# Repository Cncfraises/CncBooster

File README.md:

# CncBooster
CncBooster est un interpolateur USB basé sur le projet TinyG de Synthetos.

CncBooster is an usb motion controller board based on Synthetos TinyG project.

Christophe / 2015

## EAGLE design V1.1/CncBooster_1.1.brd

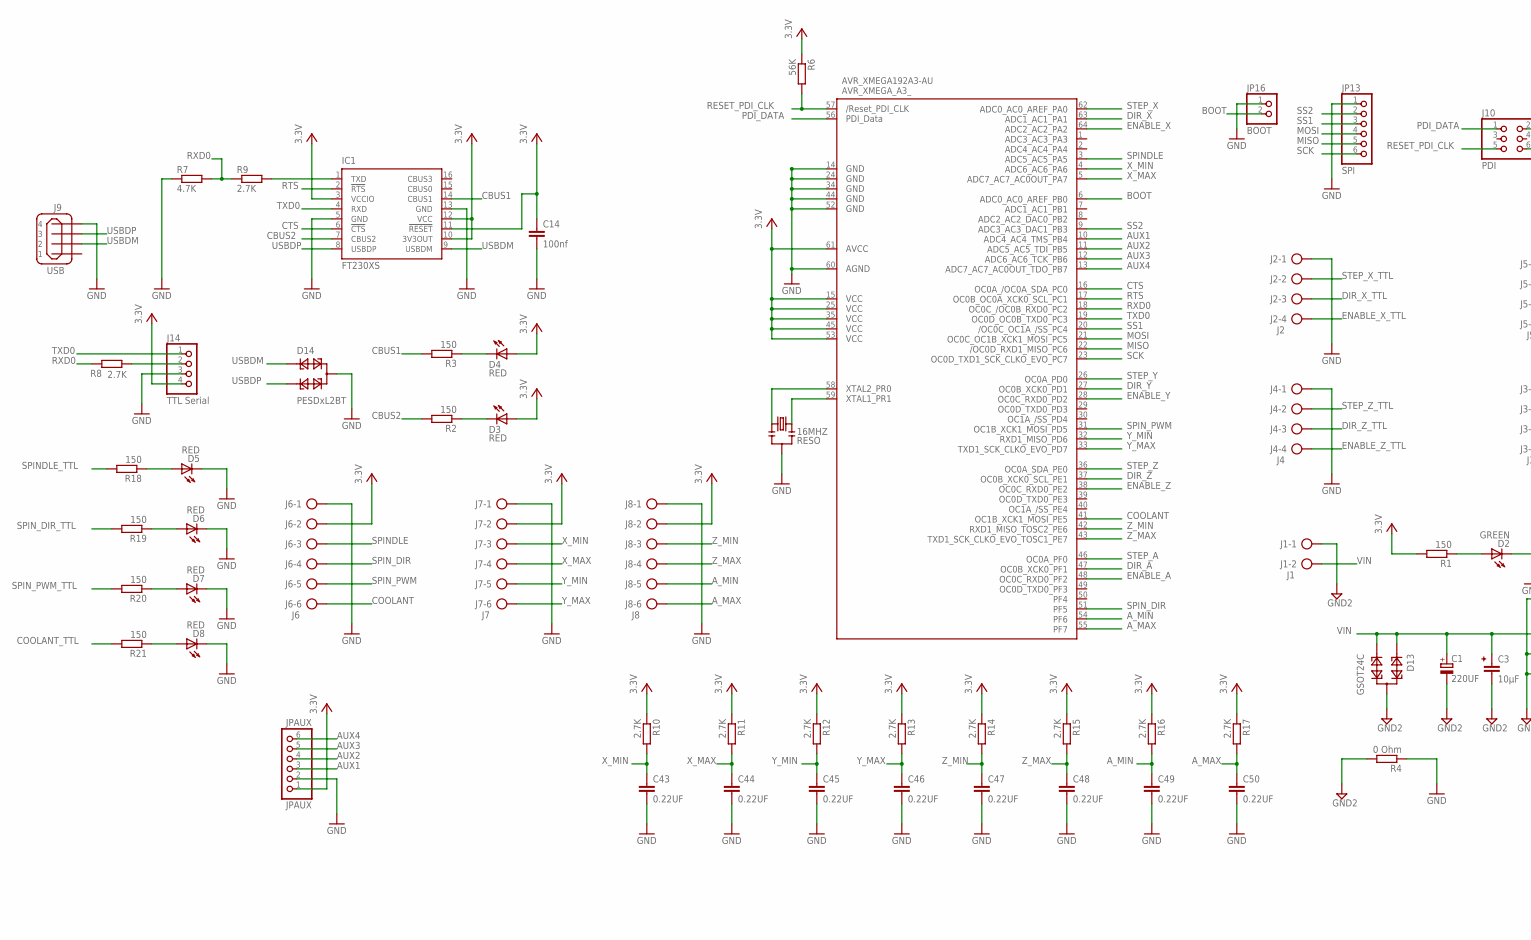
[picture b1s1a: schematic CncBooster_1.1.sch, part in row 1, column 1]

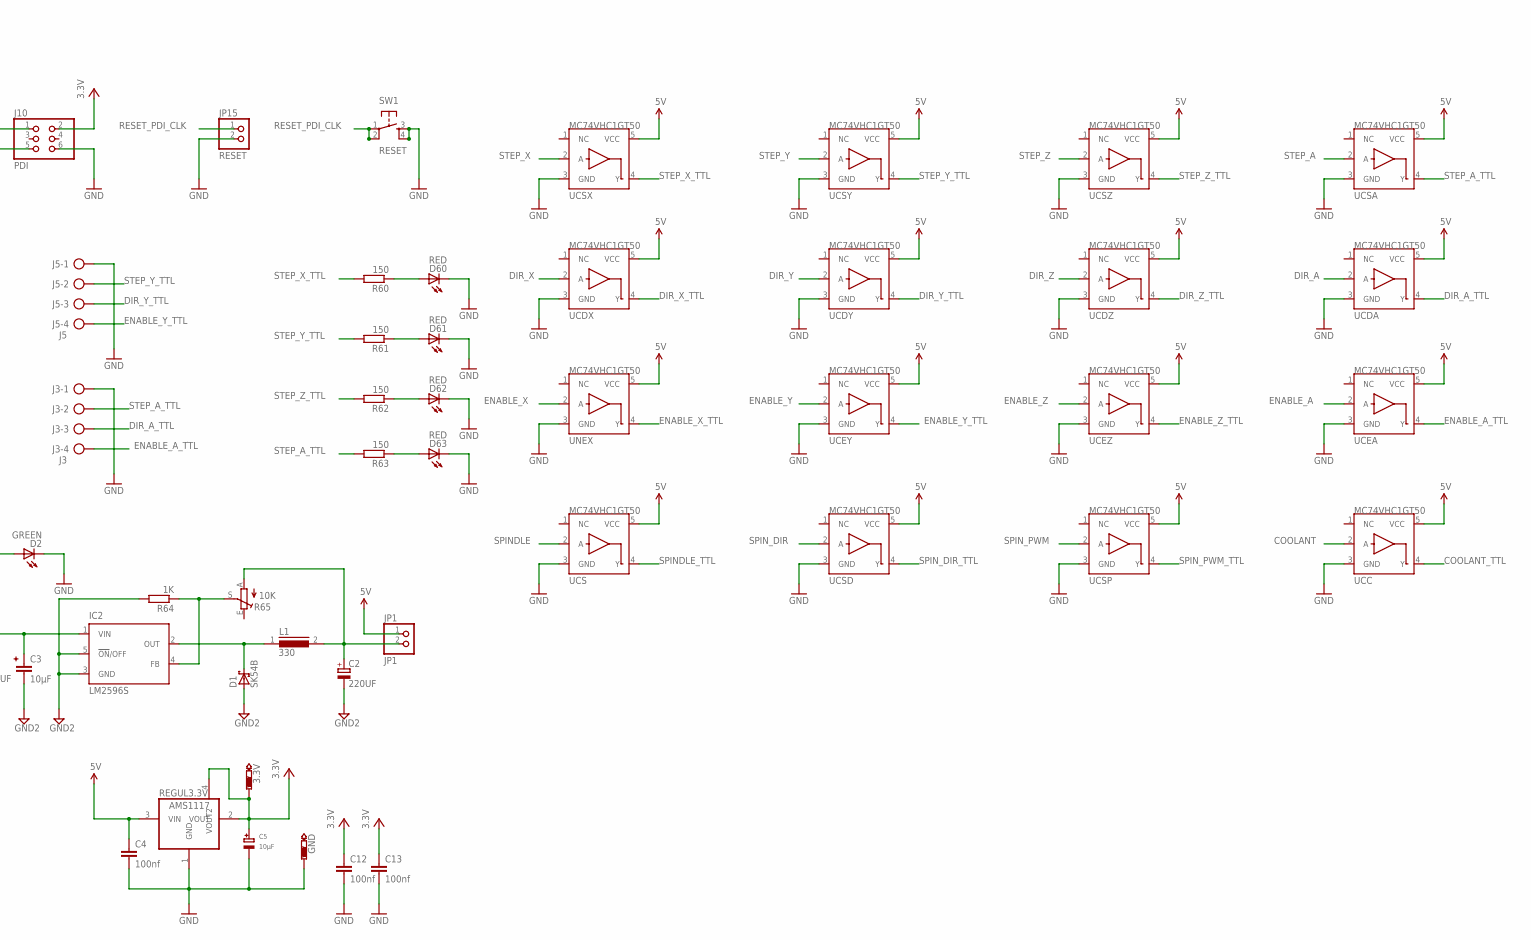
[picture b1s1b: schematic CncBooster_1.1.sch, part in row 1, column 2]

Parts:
3.3V: PTR1B1,27; B1,27
16MHZ: RESO; RESONATOR_CMS_AWSCR
AVR_XMEGA192A3-AU: AVR_XMEGA_A3_; TQFP64
C1, C2: 220UF; PANASONIC_E
C3: 10µF; CONDO_1206
C4, C12, C13, C14: 100nf; C1206
C5: 10µF; EIA3216-18/A-W
C43, C44, C45, C46, C47, C48, C49, C50: 0.22UF; C1206
D1: SK54B; DO-214AA
D2: GREEN; CHIPLED_1206
D3, D4, D5, D6, D7, D8, D60, D61, D62, D63: RED; CHIPLED_1206
D13: GSOT24C; SOT23
D14: PESDxL2BT; SOT23
GND: PTR1B1,27; B1,27
IC1: FT230XS; SSOP16
IC2: LM2596S; TO263-5
J1: J1; AK500/2
J2: J2; AK500/4
J3: J3; AK500/4
J4: J4; AK500/4
J5: J5; AK500/4
J6: J6; AK500/6
J7: J7; AK500/6
J8: J8; AK500/6
J9: USB; 85-32004-10X
J10: PDI; 2X03
J14: TTL Serial; 1X04
JP1: JP1; 1X02
JP13: SPI; 1X06
JP15: RESET; 1X02
JP16: BOOT; 1X02
JPAUX: JPAUX; 1X06
L1: 330; DR127
R1, R2, R3, R18, R19, R20, R21, R60, R61, R62, R63: 150; R1206
R4: 0 Ohm; R1206
R6: 56K; R1206
R7: 4.7K; R1206
R8, R9, R10, R11, R12, R13, R14, R15, R16, R17: 2.7K; R1206
R64: 1K; R1206
R65: 10K; S64W
REGUL3.3V: AMS1117; SOT223-A
SW1: RESET; TACTILE_SWITCH_SMD
UCC: MC74VHC1GT50; SOT23-5
UCDA: MC74VHC1GT50; SOT23-5
UCDX: MC74VHC1GT50; SOT23-5
UCDY: MC74VHC1GT50; SOT23-5
UCDZ: MC74VHC1GT50; SOT23-5
UCEA: MC74VHC1GT50; SOT23-5
UCEY: MC74VHC1GT50; SOT23-5
UCEZ: MC74VHC1GT50; SOT23-5
UCS: MC74VHC1GT50; SOT23-5
UCSA: MC74VHC1GT50; SOT23-5
UCSD: MC74VHC1GT50; SOT23-5
UCSP: MC74VHC1GT50; SOT23-5
UCSX: MC74VHC1GT50; SOT23-5
UCSY: MC74VHC1GT50; SOT23-5
UCSZ: MC74VHC1GT50; SOT23-5
UNEX: MC74VHC1GT50; SOT23-5

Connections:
5V: C4.1, JP1.1, REGUL3.3V.3 (VIN), UCC.5 (VCC), UCDA.5 (VCC), UCDX.5 (VCC), UCDY.5 (VCC), UCDZ.5 (VCC), UCEA.5 (VCC), UCEY.5 (VCC), UCEZ.5 (VCC), UCS.5 (VCC), UCSA.5 (VCC), UCSD.5 (VCC), UCSP.5 (VCC), UCSX.5 (VCC), UCSY.5 (VCC), UCSZ.5 (VCC), UNEX.5 (VCC)
AUX1: AVR_XMEGA192A3-AU.10 (PB4), JPAUX.3
AUX2: AVR_XMEGA192A3-AU.11 (PB5), JPAUX.4
AUX3: AVR_XMEGA192A3-AU.12 (PB6), JPAUX.5
AUX4: AVR_XMEGA192A3-AU.13 (PB7), JPAUX.6
A_MAX: AVR_XMEGA192A3-AU.55 (PF7), C50.1, J8.6, R17.2
A_MIN: AVR_XMEGA192A3-AU.54 (PF6), C49.1, J8.5, R16.2
BOOT: AVR_XMEGA192A3-AU.6 (PB0), JP16.2
CBUS1: IC1.14 (CBUS1), R3.2
CBUS2: IC1.7 (CBUS2), R2.2
COOLANT: AVR_XMEGA192A3-AU.41 (PE5), J6.6, UCC.2 (A)
COOLANT_TTL: R21.2, UCC.4 (Y)
CTS: AVR_XMEGA192A3-AU.16 (PC0), IC1.6 (!CTS)
DIR_A: AVR_XMEGA192A3-AU.47 (PF1), UCDA.2 (A)
DIR_A_TTL: J3.3, UCDA.4 (Y)
DIR_X: AVR_XMEGA192A3-AU.63 (PA1), UCDX.2 (A)
DIR_X_TTL: J2.3, UCDX.4 (Y)
DIR_Y: AVR_XMEGA192A3-AU.27 (PD1), UCDY.2 (A)
DIR_Y_TTL: J5.3, UCDY.4 (Y)
DIR_Z: AVR_XMEGA192A3-AU.37 (PE1), UCDZ.2 (A)
DIR_Z_TTL: J4.3, UCDZ.4 (Y)
ENABLE_A: AVR_XMEGA192A3-AU.48 (PF2), UCEA.2 (A)
ENABLE_A_TTL: J3.4, UCEA.4 (Y)
ENABLE_X: AVR_XMEGA192A3-AU.64 (PA2), UNEX.2 (A)
ENABLE_X_TTL: J2.4, UNEX.4 (Y)
ENABLE_Y: AVR_XMEGA192A3-AU.28 (PD2), UCEY.2 (A)
ENABLE_Y_TTL: J5.4, UCEY.4 (Y)
ENABLE_Z: AVR_XMEGA192A3-AU.38 (PE2), UCEZ.2 (A)
ENABLE_Z_TTL: J4.4, UCEZ.4 (Y)
GND: 16MHZ.P$3 (2), AVR_XMEGA192A3-AU.14 (GND1), AVR_XMEGA192A3-AU.24 (GND2), AVR_XMEGA192A3-AU.34 (GND3), AVR_XMEGA192A3-AU.44 (GND4), AVR_XMEGA192A3-AU.52 (GND5), AVR_XMEGA192A3-AU.60 (AGND), C4.2, C5.-, C12.2, C13.2, C14.2, C43.2, C44.2, C45.2, C46.2, C47.2, C48.2, C49.2, C50.2, D2.C, D5.C, D6.C, D7.C, D8.C, D14.3, D60.C, D61.C, D62.C, D63.C, GND.TP, IC1.5 (GND), IC1.13 (GND), J2.1, J3.1, J4.1, J5.1, J6.1, J7.1, J8.1, J9.4, J10.6, J14.3, JP13.1, JP15.2, JP16.1, JPAUX.2, R4.1, R7.1, REGUL3.3V.1 (GND), SW1.3, SW1.4, UCC.3 (GND), UCDA.3 (GND), UCDX.3 (GND), UCDY.3 (GND), UCDZ.3 (GND), UCEA.3 (GND), UCEY.3 (GND), UCEZ.3 (GND), UCS.3 (GND), UCSA.3 (GND), UCSD.3 (GND), UCSP.3 (GND), UCSX.3 (GND), UCSY.3 (GND), UCSZ.3 (GND), UNEX.3 (GND)
GND2: C1.-, C2.-, C3.1 (2), D1.A, D13.3, IC2.3 (GND), IC2.5 (!ON!/OFF), J1.1, R4.2, R64.2
MISO: AVR_XMEGA192A3-AU.22 (PC6), JP13.5
MOSI: AVR_XMEGA192A3-AU.21 (PC5), JP13.4
unnamed: 16MHZ.P$2 (3), AVR_XMEGA192A3-AU.59 (PR1)
unnamed: 16MHZ.P$1 (1), AVR_XMEGA192A3-AU.58 (PR0)
unnamed: D3.C, R2.1
unnamed: D4.C, R3.1
unnamed: J14.2, R8.1
unnamed: IC1.1 (TXD), R9.2
unnamed: D5.A, R18.1
unnamed: D6.A, R19.1
unnamed: D7.A, R20.1
unnamed: D8.A, R21.1
unnamed: D60.A, R60.1
unnamed: D61.A, R61.1
unnamed: D62.A, R62.1
unnamed: D63.A, R63.1
unnamed: D1.C, IC2.2 (OUT), L1.1
unnamed: IC2.4 (FB), R64.1, R65.S
unnamed: D2.A, R1.1
unnamed: C2.+, JP1.2, L1.2, R65.A
PDI_DATA: AVR_XMEGA192A3-AU.56 (PDI_DATA), J10.1
RESET_PDI_CLK: AVR_XMEGA192A3-AU.57 (RESET), J10.5, JP15.1, R6.2, SW1.1, SW1.2
RTS: AVR_XMEGA192A3-AU.17 (PC1), IC1.2 (!RTS)
RXD0: AVR_XMEGA192A3-AU.18 (PC2), R7.2, R8.2, R9.1
SCK: AVR_XMEGA192A3-AU.23 (PC7), JP13.6
SPINDLE: AVR_XMEGA192A3-AU.3 (PA5), J6.3, UCS.2 (A)
SPINDLE_TTL: R18.2, UCS.4 (Y)
SPIN_DIR: AVR_XMEGA192A3-AU.51 (PF5), J6.4, UCSD.2 (A)
SPIN_DIR_TTL: R19.2, UCSD.4 (Y)
SPIN_PWM: AVR_XMEGA192A3-AU.31 (PD5), J6.5, UCSP.2 (A)
SPIN_PWM_TTL: R20.2, UCSP.4 (Y)
SS1: AVR_XMEGA192A3-AU.20 (PC4), JP13.3
SS2: AVR_XMEGA192A3-AU.9 (PB3), JP13.2
STEP_A: AVR_XMEGA192A3-AU.46 (PF0), UCSA.2 (A)
STEP_A_TTL: J3.2, R63.2, UCSA.4 (Y)
STEP_X: AVR_XMEGA192A3-AU.62 (PA0), UCSX.2 (A)
STEP_X_TTL: J2.2, R60.2, UCSX.4 (Y)
STEP_Y: AVR_XMEGA192A3-AU.26 (PD0), UCSY.2 (A)
STEP_Y_TTL: J5.2, R61.2, UCSY.4 (Y)
STEP_Z: AVR_XMEGA192A3-AU.36 (PE0), UCSZ.2 (A)
STEP_Z_TTL: J4.2, R62.2, UCSZ.4 (Y)
TXD0: AVR_XMEGA192A3-AU.19 (PC3), IC1.4 (RXD), J14.1
USBDM: D14.1, IC1.9 (USBDM), J9.2
USBDP: D14.2, IC1.8 (USBDP), J9.3
VCC: 3.3V.TP, AVR_XMEGA192A3-AU.15 (VCC1), AVR_XMEGA192A3-AU.25 (VCC2), AVR_XMEGA192A3-AU.35 (VCC3), AVR_XMEGA192A3-AU.45 (VCC4), AVR_XMEGA192A3-AU.53 (VCC5), AVR_XMEGA192A3-AU.61 (AVCC), C5.+, C12.1, C13.1, C14.1, D3.A, D4.A, IC1.3 (VCCIO), IC1.10 (3V3OUT), IC1.11 (!RESET), IC1.12 (VCC), J6.2, J7.2, J8.2, J10.2, J14.4, JPAUX.1, R1.2, R6.1, R10.1, R11.1, R12.1, R13.1, R14.1, R15.1, R16.1, R17.1, REGUL3.3V.2 (VOUT), REGUL3.3V.4 (VOUT2)
VIN: C1.+, C3.2 (1), D13.1, D13.2, IC2.1 (VIN), J1.2
X_MAX: AVR_XMEGA192A3-AU.5 (PA7), C44.1, J7.4, R11.2
X_MIN: AVR_XMEGA192A3-AU.4 (PA6), C43.1, J7.3, R10.2
Y_MAX: AVR_XMEGA192A3-AU.33 (PD7), C46.1, J7.6, R13.2
Y_MIN: AVR_XMEGA192A3-AU.32 (PD6), C45.1, J7.5, R12.2
Z_MAX: AVR_XMEGA192A3-AU.43 (PE7), C48.1, J8.4, R15.2
Z_MIN: AVR_XMEGA192A3-AU.42 (PE6), C47.1, J8.3, R14.2

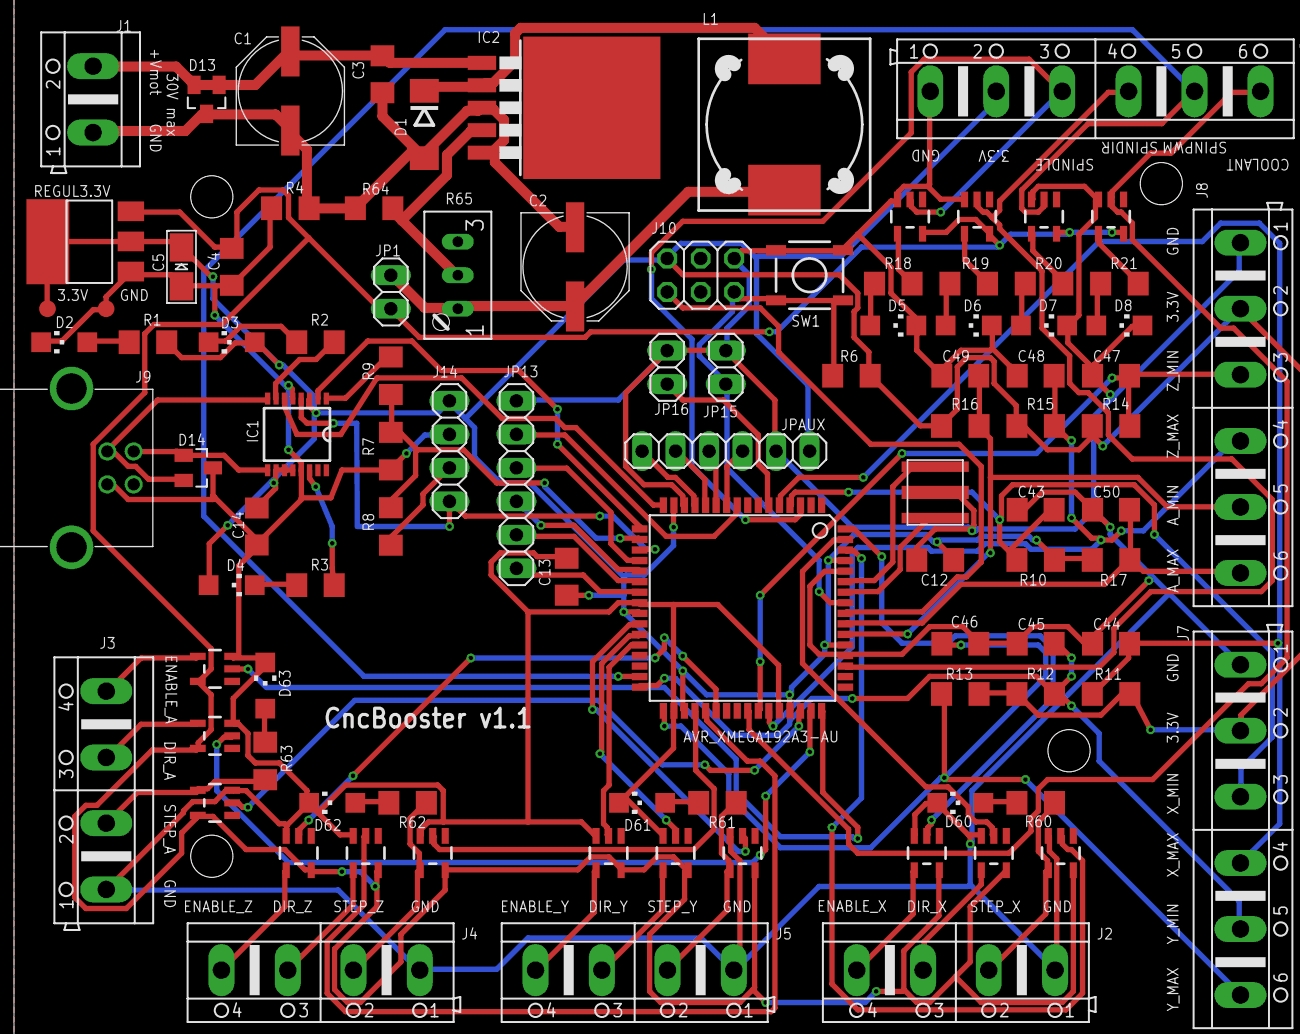
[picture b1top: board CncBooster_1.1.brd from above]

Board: 2 copper layers, 97 parts (0 on the bottom side), 83 nets.

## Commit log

2015-10-11 Version initiale du projet
2015-10-11 Modification du nom de la carte sur le PCB

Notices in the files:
parts and their libraries:
microbuilder: This work is placed in the public domain, and may be freely used for commercial and non-commercial work with the following conditions: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
SparkFun3: Licensing: CC v3.0 Share-Alike You are welcome to use this library for commercial purposes.
